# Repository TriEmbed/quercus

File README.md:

# Quercus (NOTE: Project name will change soon)
Quercus is a standalone system for developing for and using the combination of
a WIFI-capable ESP32 and one or more Renesas/Dialog mixed signal FPGA
chips. The FPGA synthesis tool has a drag and drop GUI that involves zero
Verilog or VHDL. It has a built in simulator and generates files that Quercus
can program in place in the user's system for simple FPGA applications. These
FPGAs are around one to two dollars in single quantity, even ones mounted on a
DIP board that can plug into a wireless breadboard. Quercus is aimed at making
FPGAs available to "the rest of us" while also creating a development ecosystem
to augment the Espressif IDF and Arduino IDE.

## User group
The user group kickoff meeting was held on 8/31/2022. Video here: https://youtu.be/zqejgwW3aIo

## Installation

### Linux

The first thing that should be done is run the script below with it's help
screen as such:

``` console
$ ./linux_install.sh --help
Usage: linux_install.sh -[3bcdhprstD] --[c3board,target-branch,config,device,help,wifi-passwd,rewrite-config,target,debug]
    -3 NUM | --c3board NUM              - The version of the que_purple board either 60 | 70, defaults to 70.
    -c FILE | --config FILE             - Optional config file, defaults to .quercusrc
    -d DEVICE | --device DEVICE         - Can be one of ESP32 | ESP32C3 | ESP32S2 defaults to ESP32C3.
    -h | --help                         - This screen.
    -p PASSWD | --wifi-passwd PASSWD    - The Password for the SSID.
    -r | --rewrite-config               - Reprompts for entries then rewrites the config file.
    -s SSID | --wifi-ssid SSID          - The WiFi SSID in the current network.
    -t TARGET_DIR | --target TARGET_DIR - The directory where the build will reside, defaults to /home/cnobile/.quercus.
    -D | --debug                        - Turn on DEBUG mode (propagates to the installit.sh script)..
    -n | --noop                         - The installit.sh script will not run, but the config may still be created.

    I2C pins as follows
    -------------------
      ESP32: SDA 18 SCL 19
    ESP32S2: SDA 1  SCL 0
    ESP32C3: SDA 18 SCL 19 (m80 60 rev)
             SDA 1  SCL 0  (m80 70 rev)
```

The ```linux_install.sh``` script can be run in multiple ways which will be
reviewed below. This script has the ability to create and use a config file.
The config file ```.quercusrc``` can be located in either the base of the
Quercus directory or in your user directory. The script will find the config
file in either place but will favor the Quercus directory.

1. To create a config file run the script with no arguments on the first
   run. If you need to rewrite the config file use the ```-r``` or 
   ```--rewrite-config``` argument.

   ``` bash
   $ ./linux_install.sh
   ```
   or
   ``` bash
   $ ./linux_install.sh -r
   ```
   The prompts will look similar to the ones below.
   ``` console
   Enter WiFi SSID or if exists Default () [Dd]: My-SSID
   Enter WiFi passwd or if exists Default () [Dd]: My-SSID-password
   Enter target device or Default (ESP32C3) [Dd]: ESP32
   Enter target directory or Default (/home/<user>/.quercus) [Dd]: /home/<user>/projects
   Enter target branch or Default (origin/release/v4.4) [Dd]: d
   ```
   Pressing **D** or **d** will use the default value. Use this if there is a
   default value between the **()**. Entering a space is NOT allowed and will
   cause the prompt to be displayed again. See 5 below.

   The generated config file will always be put in the base of the Quercus
   repository, if you want it in your user home directory you will need to
   manually move it there. The ```linux_install.sh``` script will find it as
   long as there is not a ```.quercusrc``` file in the Quercus directory.

2. You can also use a config file with a different name as shown below. This
   can allow you to have a config for many different physical environments. You
   must add the ```-r``` argument if you already have a ```.quercusrc``` file.

   ``` bash
   $ ./linux_install.sh -rc my_my.conf
   ```
   Just enter the filename **not** the full path as it will not be found. Once
   again it will be put into the base of the Quercus repository. It is
   advisable to move any of your own files to your user directory so it cannot
   be accidentally committed into the repository.

3. In all the cases above the script will run to completion after writing the
   config file. If you just want to write out the config file add a ```-n``` to
   the command line as below.

    ``` bash
    $ ./linux_install.sh -n
   ```
   This can be used with any other arguments. For example the ```-r``` argument
   so you can rewrite the config but not run the rest of the script.

4. You can also turn on debugging which can be used with any other arguments.

   ``` bash
   $ ./linux_install.sh -nD
   ```
   Assuming there is already a config file the above will just print out all
   the variable names and their values if any then exit. If you do not have a
   config file it will prompt for all values that are required and write them
   to the config file.

5. In some cases you may **not** want your WiFi credentials in a config file.
   To do this just type anything like the word **invalid** when prompted for
   either or both values then be sure to use the command line arguments ```-s
   <ssid>``` and ```-p <ssid password>``` to override what is in the config
   file.

   ``` bash
   $ ./linux_install.sh -r -s <my real SSID> -p <my real SSID password>
   ```
   ``` console
   Enter WiFi SSID or if exists Default () [Dd]: invalid
   Enter WiFi passwd or if exists Default () [Dd]: invalid
   ...
   ```
   The above command will force a rewrite of the config file then run the
   installation code. The ```-s <my real SSID>``` and ```-p <my real SSID
   password>``` arguments override the dummy SSID and it's password. This must
   be done every time you rerun the script if you have put dummy values in your
   config file.

All the remaining arguments are used to override what is in the config file and
will not be saved to the config file. As such you can use them to override any
or all arguments that are in the config file.

### Windows

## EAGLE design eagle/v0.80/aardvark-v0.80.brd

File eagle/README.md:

# Hardware CAD and related files for combination Espressif ESP32-C3-M1 (4M) and Dialog SLG47004V-DIP

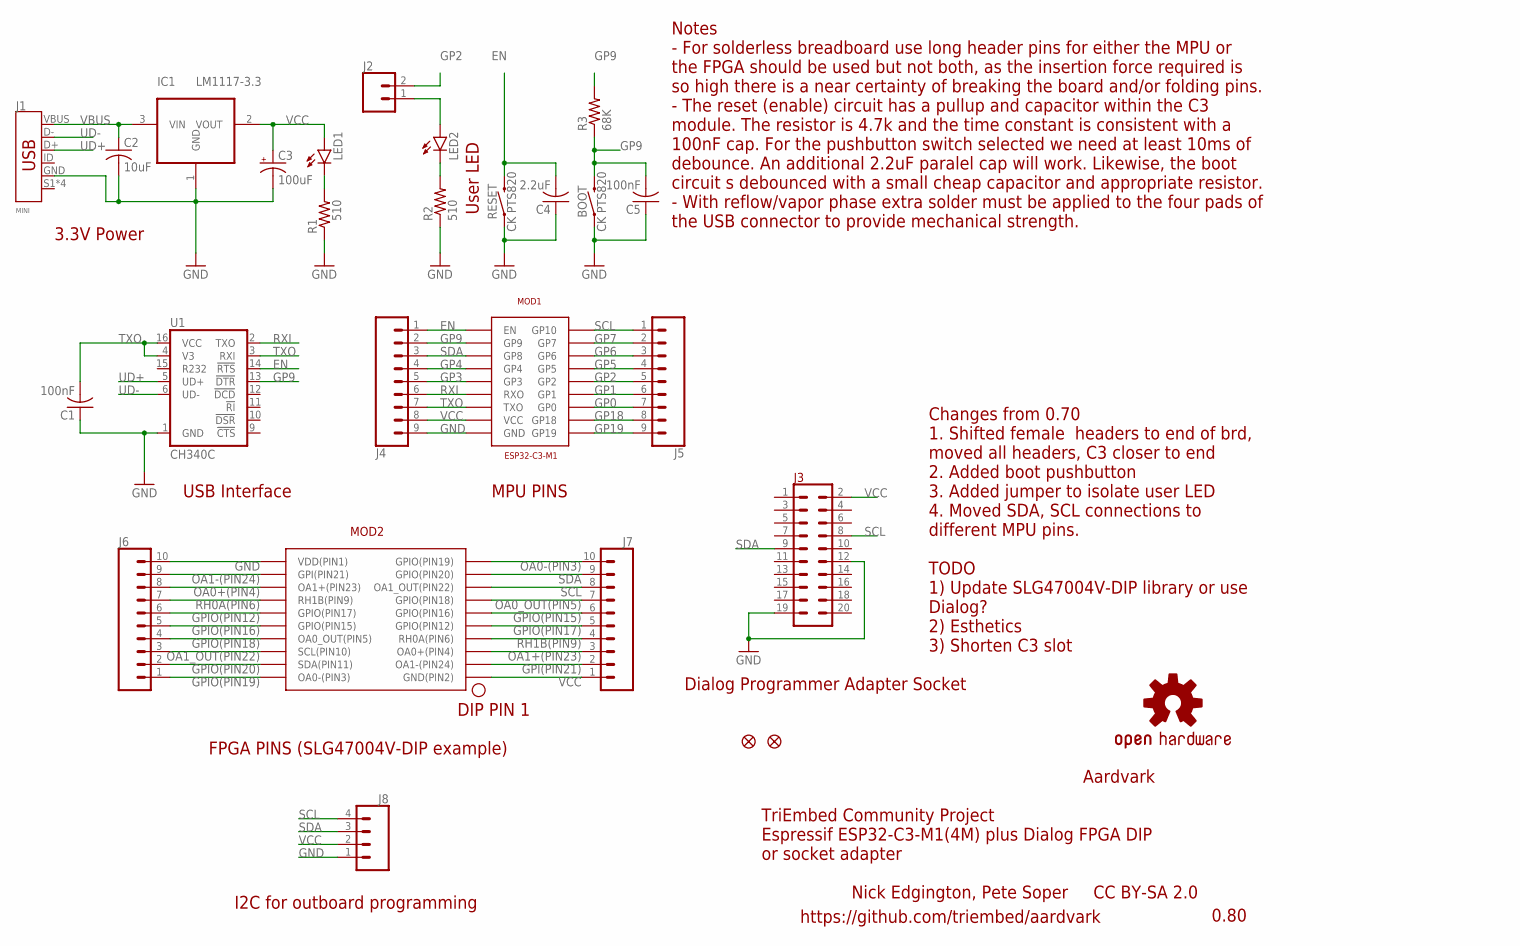
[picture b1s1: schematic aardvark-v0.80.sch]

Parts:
BOOT: CK PTS820; TACTILE_SWITCH_SMD_6.0X3.5MM
C1, C5: 100nF; C0805
C2: 10uF; C0805
C3: 100uF; PANASONIC_D
C4: 2.2uF; C0805
FD1, FD2: FIDUCIAL1X2; FIDUCIAL-1X2
IC1: LM1117-3.3; SOT223
J1: MINI; USB-MINIB
J2: CONN_02; 1X02
J3: CONN_10X2; 2X10
J4, J5: CONN_09NO_SILK; 1X09_NO_SILK
J6, J7: CONN_10NO_SILK_PTH_FEMALE; 1X10_NO_SILK
J8: CONN_041X04_NO_SILK; 1X04_NO_SILK
LED1, LED2: LEDCHIP-LED0805; CHIP-LED0805
LOGO1: OSHW-LOGOMINI; OSHW-LOGO-MINI
MOD1: ESP32-C3-M1; AITHINKER-C3-M1
MOD2: SLG47004V_DIP; SLG47004V-DIP
R1, R2: 510; R0805
R3: 68K; R0805
RESET: CK PTS820; TACTILE_SWITCH_SMD_6.0X3.5MM
U1: CH340C; SO016

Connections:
EN: C4.2, J4.1, MOD1.PIN1 (EN), RESET.2, U1.14 (!RTS)
GND: BOOT.1, C1.1, C2.2, C3.-, C4.1, C5.1, IC1.1 (GND), J1.GND, J3.12, J3.19, J4.9, J6.10, J8.1, MOD1.PIN9 (GND), MOD2.1 (VDD(PIN1)), R1.1, R2.1, RESET.1, U1.1 (GND)
GP0: J5.7, MOD1.PIN12 (GP0)
GP1: J5.6, MOD1.PIN13 (GP1)
GP2: J2.1, J2.2, J5.5, LED2.A, MOD1.PIN14 (GP2)
GP3: J4.5, MOD1.PIN5 (GP3)
GP4: J4.4, MOD1.PIN4 (GP4)
GP5: J5.4, MOD1.PIN15 (GP5)
GP6: J5.3, MOD1.PIN16 (GP6)
GP7: J5.2, MOD1.PIN17 (GP7)
GP9: BOOT.2, C5.2, J4.2, MOD1.PIN2 (GP9), R3.1, R3.2, U1.13 (!DTR)
GP18: J5.8, MOD1.PIN11 (GP18)
GP19: J5.9, MOD1.PIN10 (GP19)
GPI(PIN21): J7.2, MOD2.12 (OA1-(PIN24))
GPIO(PIN12): J6.6, MOD2.5 (GPIO(PIN17))
GPIO(PIN15): J7.6, MOD2.16 (GPIO(PIN16))
GPIO(PIN16): J6.5, MOD2.6 (GPIO(PIN15))
GPIO(PIN17): J7.5, MOD2.15 (GPIO(PIN12))
GPIO(PIN18): J6.4, MOD2.7 (OA0_OUT(PIN5))
GPIO(PIN19): J6.1, MOD2.10 (OA0-(PIN3))
GPIO(PIN20): J6.2, MOD2.9 (SDA(PIN11))
unnamed: LED2.C, R2.2
unnamed: LED1.C, R1.2
OA0+(PIN4): J6.8, MOD2.3 (OA1+(PIN23))
OA0-(PIN3): J7.10, MOD2.20 (GPIO(PIN19))
OA0_OUT(PIN5): J7.7, MOD2.17 (GPIO(PIN18))
OA1+(PIN23): J7.3, MOD2.13 (OA0+(PIN4))
OA1-(PIN24): J6.9, MOD2.2 (GPI(PIN21))
OA1_OUT(PIN22): J6.3, MOD2.8 (SCL(PIN10))
RH0A(PIN6): J6.7, MOD2.4 (RH1B(PIN9))
RH1B(PIN9): J7.4, MOD2.14 (RH0A(PIN6))
RXI: J4.6, MOD1.PIN6 (RXO), U1.2 (TXO)
SCL: J3.8, J5.1, J7.8, J8.4, MOD1.PIN18 (GP10), MOD2.18 (OA1_OUT(PIN22))
SDA: J3.9, J4.3, J7.9, J8.3, MOD1.PIN3 (GP8), MOD2.19 (GPIO(PIN20))
TXO: C1.2, J4.7, MOD1.PIN7 (TXO), U1.3 (RXI), U1.4 (V3), U1.16 (VCC)
UD+: J1.D+, U1.5 (UD+)
UD-: J1.D-, U1.6 (UD-)
VBUS: C2.1, IC1.3 (VIN), J1.VBUS
VCC: C3.+, IC1.2 (VOUT), J3.2, J4.8, J7.1, J8.2, LED1.A, MOD1.PIN8 (VCC), MOD2.11 (GND(PIN2))

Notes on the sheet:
0.80
Aardvark
TriEmbed Community Project Espressif ESP32-C3-M1(4M) plus Dialog FPGA DIP or socket adapter
Nick Edgington, Pete Soper CC BY-SA 2.0
https://github.com/triembed/aardvark
FPGA PINS (SLG47004V-DIP example)
MPU PINS
USB Interface
3.3V Power
User LED
Dialog Programmer Adapter Socket
I2C for outboard programming
Notes - For solderless breadboard use long header pins for either the MPU or the FPGA should be used but not both, as the insertion force required is so high there is a near certainty of breaking the board and/or folding pins. - The reset (enable) circuit has a pullup and capacitor within the C3 mo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
Changes from 0.70 1. Shifted female headers to end of brd, moved all headers, C3 closer to end 2. Added boot pushbutton 3. Added jumper to isolate user LED 4. Moved SDA, SCL connections to different MPU pins.
DIP PIN 1
TODO 1) Update SLG47004V-DIP library or use Dialog? 2) Esthetics 3) Shorten C3 slot

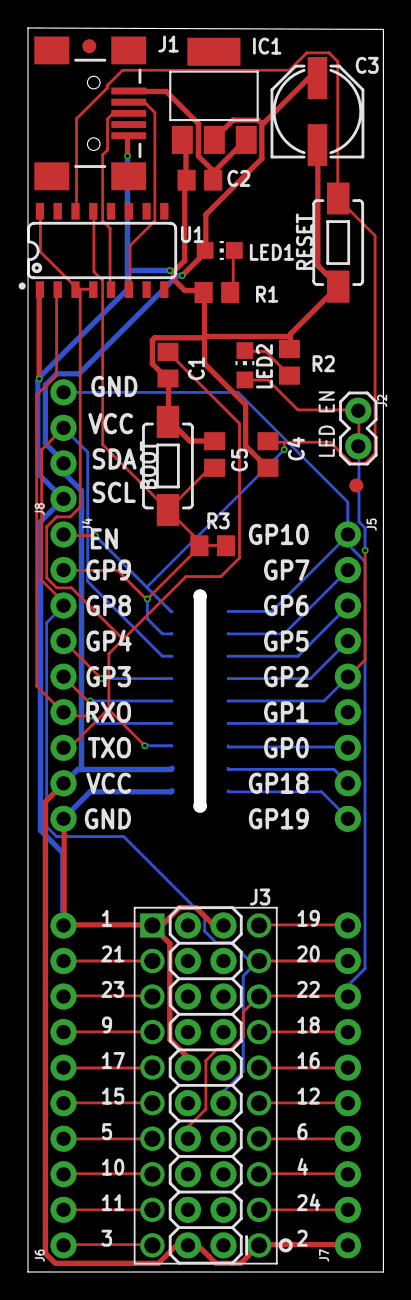
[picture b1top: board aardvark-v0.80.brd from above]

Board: 2 copper layers, 25.4 x 88.9 mm, 27 parts (1 on the bottom side), 39 nets.

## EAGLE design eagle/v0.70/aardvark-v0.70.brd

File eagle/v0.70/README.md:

# This is the 0.70 version of the ESP32 C3 + SLG47004V-DIP board.

## Changes since 0.60
1. Add switches for Enable, GPIO8, GPIO9 for reset and boot control
2. 4.7uF from Enable to ground to stretch it's time spent low
3. I2C pullups changed to 10k 'cause the signal paths are very short
4. Improve labeling
5. Spell aardvark correctly
6. Fix mirror image label ("GND")

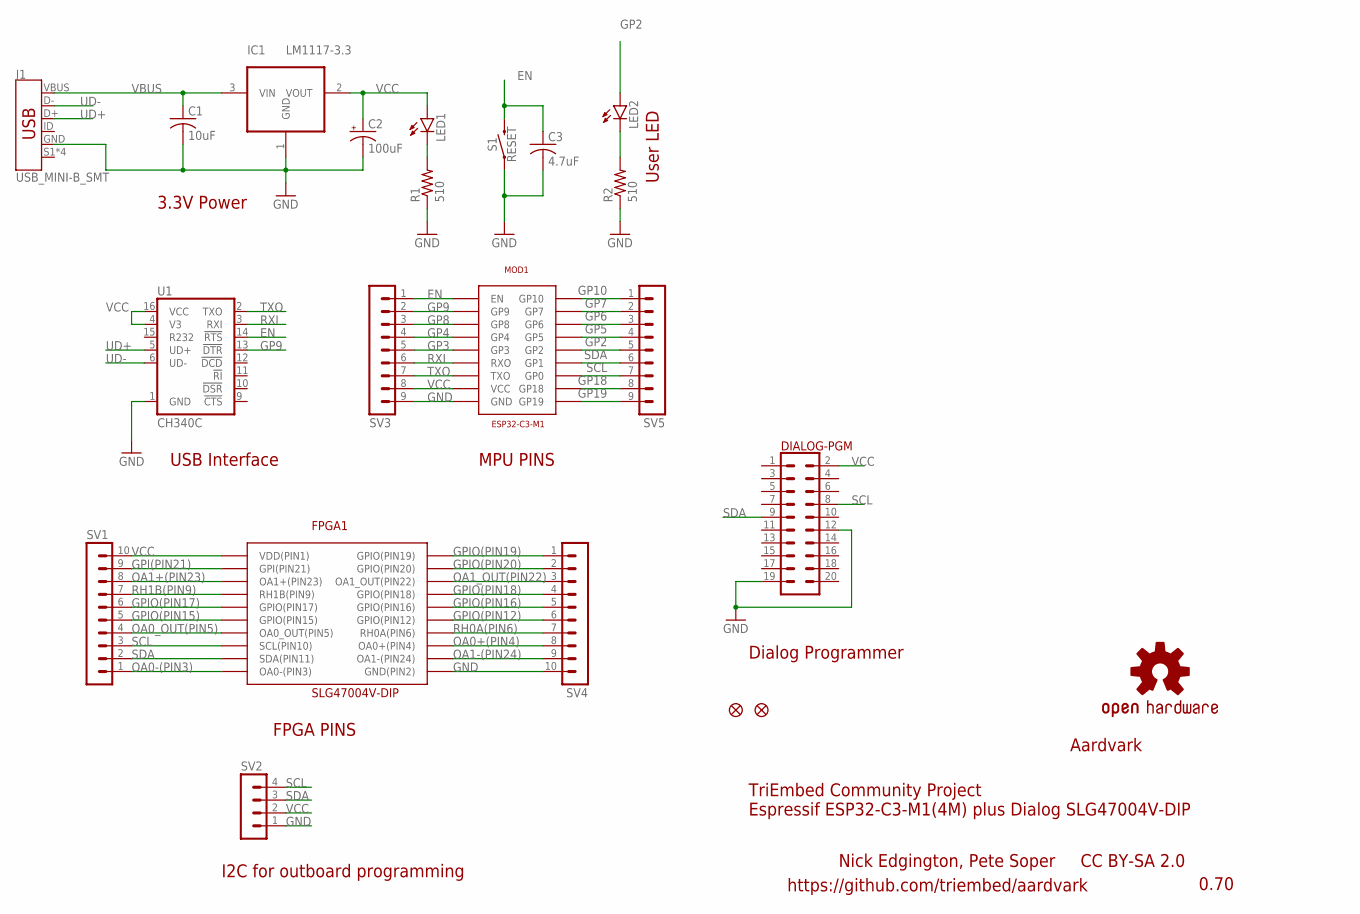
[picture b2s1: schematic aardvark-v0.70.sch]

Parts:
C1: 10uF; C0805
C2: 100uF; PANASONIC_D
C3: 4.7uF; C0805
DIALOG-PGM: CONN_10X2; 2X10
FD1, FD2: FIDUCIAL1X2; FIDUCIAL-1X2
FPGA1: SLG47004V-DIP
IC1: LM1117-3.3; SOT223
J1: USB_MINI-B_SMT; USB-MINIB
LED1, LED2: LEDCHIP-LED0805; CHIP-LED0805
LOGO1: OSHW-LOGOMINI; OSHW-LOGO-MINI
MOD1: ESP32-C3-M1; AITHINKER-C3-M1
R1, R2: 510; R0805
S1: RESET; TACTILE_SWITCH_SMD_6.0X3.5MM
SV1, SV4: MA10-1
SV2: MA04-1
SV3, SV5: MA09-1
U1: CH340C; SO016

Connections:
EN: C3.1, MOD1.PIN1 (EN), S1.2, SV3.1, U1.14 (!RTS)
GND: C1.2, C2.-, C3.2, DIALOG-PGM.12, DIALOG-PGM.19, FPGA1.11 (GND(PIN2)), IC1.1 (GND), J1.GND, MOD1.PIN9 (GND), R1.1, R2.1, S1.1, SV2.1, SV3.9, SV4.10, U1.1 (GND)
GP2: LED2.A, MOD1.PIN14 (GP2), SV5.5
GP3: MOD1.PIN5 (GP3), SV3.5
GP4: MOD1.PIN4 (GP4), SV3.4
GP5: MOD1.PIN15 (GP5), SV5.4
GP6: MOD1.PIN16 (GP6), SV5.3
GP7: MOD1.PIN17 (GP7), SV5.2
GP8: MOD1.PIN3 (GP8), SV3.3
GP9: MOD1.PIN2 (GP9), SV3.2, U1.13 (!DTR)
GP10: MOD1.PIN18 (GP10), SV5.1
GP18: MOD1.PIN11 (GP18), SV5.8
GP19: MOD1.PIN10 (GP19), SV5.9
GPI(PIN21): FPGA1.2 (GPI(PIN21)), SV1.9
GPIO(PIN12): FPGA1.15 (GPIO(PIN12)), SV4.6
GPIO(PIN15): FPGA1.6 (GPIO(PIN15)), SV1.5
GPIO(PIN16): FPGA1.16 (GPIO(PIN16)), SV4.5
GPIO(PIN17): FPGA1.5 (GPIO(PIN17)), SV1.6
GPIO(PIN18): FPGA1.17 (GPIO(PIN18)), SV4.4
GPIO(PIN19): FPGA1.20 (GPIO(PIN19)), SV4.1
GPIO(PIN20): FPGA1.19 (GPIO(PIN20)), SV4.2
unnamed: LED2.C, R2.2
unnamed: LED1.C, R1.2
OA0+(PIN4): FPGA1.13 (OA0+(PIN4)), SV4.8
OA0-(PIN3): FPGA1.10 (OA0-(PIN3)), SV1.1
OA0_OUT(PIN5): FPGA1.7 (OA0_OUT(PIN5)), SV1.4
OA1+(PIN23): FPGA1.3 (OA1+(PIN23)), SV1.8
OA1-(PIN24): FPGA1.12 (OA1-(PIN24)), SV4.9
OA1_OUT(PIN22): FPGA1.18 (OA1_OUT(PIN22)), SV4.3
RH0A(PIN6): FPGA1.14 (RH0A(PIN6)), SV4.7
RH1B(PIN9): FPGA1.4 (RH1B(PIN9)), SV1.7
RXI: MOD1.PIN6 (RXO), SV3.6, U1.3 (RXI)
SCL: DIALOG-PGM.8, FPGA1.8 (SCL(PIN10)), MOD1.PIN12 (GP0), SV1.3, SV2.4, SV5.7
SDA: DIALOG-PGM.9, FPGA1.9 (SDA(PIN11)), MOD1.PIN13 (GP1), SV1.2, SV2.3, SV5.6
TXO: MOD1.PIN7 (TXO), SV3.7, U1.2 (TXO)
UD+: J1.D+, U1.5 (UD+)
UD-: J1.D-, U1.6 (UD-)
VBUS: C1.1, IC1.3 (VIN), J1.VBUS
VCC: C2.+, DIALOG-PGM.2, FPGA1.1 (VDD(PIN1)), IC1.2 (VOUT), LED1.A, MOD1.PIN8 (VCC), SV1.10, SV2.2, SV3.8, U1.4 (V3), U1.16 (VCC)

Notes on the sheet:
0.70
Aardvark
TriEmbed Community Project Espressif ESP32-C3-M1(4M) plus Dialog SLG47004V-DIP
Nick Edgington, Pete Soper CC BY-SA 2.0
https://github.com/triembed/aardvark
FPGA PINS
MPU PINS
USB Interface
3.3V Power
User LED
Dialog Programmer
I2C for outboard programming

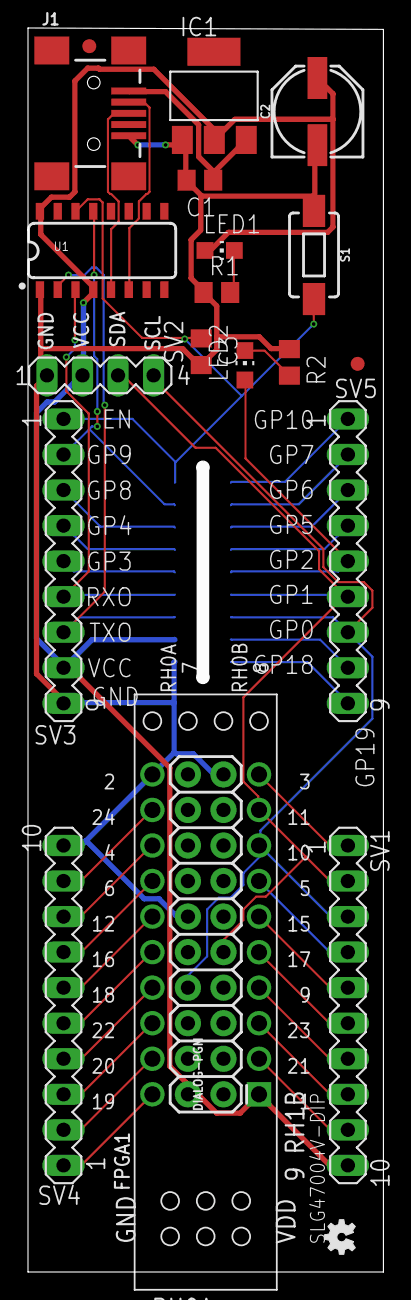
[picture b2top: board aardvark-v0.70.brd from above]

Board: 2 copper layers, 25.4 x 88.9 mm, 22 parts (0 on the bottom side), 39 nets.

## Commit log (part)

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2021-12-24 Clarification
2021-12-24 Defined versioning for README.md files
2021-12-24 test commit
2021-12-24 initial doc/contrib/Dialog/publications/README.md
2021-12-27 added doc/contrib/license/README.md
2021-12-30 prune junk
2021-12-30 additional MTP chips, prune junk
2021-12-30 doc/contrib/dialog/datasheets/README.md MTP part info
2021-12-31 added forum link to doc/contrib/dialog/publications/README.md
2021-12-31 Added oc/contrib/dialog/cad/GREENPAK.lbr, ditched useless part
2022-01-01 SLG46826G Breakout version 1.00
2022-01-01 dialog/SLG46826G-breakout version 1.00
2022-01-08 top level README.md update
2022-01-08 rename SLG46826G breakout directory
2022-01-08 rename breakout dir
2022-01-08 files moved from League repo
2022-01-08 C/C++ formatting script moved from League repo
2022-01-17 doc/contrib/ai-thinker/esp-c3-01m_specification.pdf
2022-01-19 doc/contrib/dialog/publications/SLG47004V_DIP_Proto_Board_Quick_Start_Guide.pdf
2022-01-19 removed obsolete programmer subdir
2022-01-26 Removed doc/contrib/gowin
2022-01-26 Culled irrelevant stuff from doc/contrib/dialog/datasheets
2022-01-26 updated doc/INVENTORY.md
2022-01-26 eagle/README.md wrestling
2022-01-26 culled doc/contrib/dialog/publications/README.md
2022-01-26 Added bug to README.md
2022-01-26 Added bugs and notes to top level README.md
2022-01-26 another attempt to comment out pictures
2022-01-26 images in eagle/README.md reenabled
2022-01-27 Added more bugs to top level README.md
2022-01-28 Added bugs and todo items to top level README.md. Could stand to be grouped together.
2022-01-28 added doc/README.md hyperlinks to ESP32 boot process details and little C3 dev board being used as a model implementation
2022-01-30 eagle/v0.70 initial
2022-01-31 fixed spelling error and mirror image GND designator
2022-01-31 more fixes doc'd in eagle/v0.70/README.md
2022-01-31 fixed, improved C3 Eagle lib
2022-01-31 rename C3 Eagle lib
2022-01-31 add OSH Park renderings of PCB top and bottom to eagle/v0.60
2022-01-31 boot/flash process steps put into doc/README.md
2022-02-01 Add note to bug pile item 0 in top level README.md
2022-02-01 added Eagle lib for the CH340C USB chip
2022-02-02 added Nanjin_Qinheng_Microelectronics CH340.pdf to doc/contrib
2022-02-02 added todo for adding a Dialog QFN socket/programmer footprint
2022-02-02 fixes to SLG47004V-DIP.lbr
2022-02-02 cleaned out obsolete notes
2022-02-02 Added more todos per Nick to README.md
2022-02-02 eagle/lib/README.md
2022-02-02 schematic update
2022-02-02 PDF of schematic
2022-02-02 new convension for PDFs foo-board.pdf instead of -layout.pdf
2022-02-02 really fix slot width
2022-02-02 added right angle header site for outboard I2C programming
2022-02-02 updated bug/todo list, added item for checking fit of programmer
2022-02-03 Noted shortening/narrowing of slot for C3
2022-02-03 confirmed Dialog programming socket board will not physically interfere
2022-02-04 doc/contrib/dialog/publications/README.md added URL for GreenPAKs by attribute
2022-02-04 aardvark v0.70 as shipped to OSH Park
2022-02-04 OSH Park renders of v0.70
2022-02-05 updated inventory
2022-02-06 eagle/v0.70/BOM.ods
2022-02-06 README.md updated
2022-02-06 initial firmware/README.md
2022-02-08 images/model-esp32-board.jpg has reset/boot circuit needed on our boards
2022-02-09 fixed PDFs
2022-02-09 added link to download page
2022-02-10 added three youtube videos to the bottom of doc/contrib/dialog/README.md
2022-02-11 ECOs added to eagle/v0.70/aardvark-v0.70-schematic.pdf
2022-02-11 example usage of v0.80 shown with aardvark-v0.80-board.pdf
2022-02-14 proper momentary and power switches for v0.80
2022-03-30 echidna concept2
2022-04-05 added Espressif datasheet local copy and URL
2022-04-08 eagle/v0.80 updated schematic todo list
2022-04-29 eagle/lib/{CK-ATS2D1G_NC_LFS.lbr,CK_JS202011SCQN.lbr} candidate switches
2022-05-15 English
2022-05-16 some tests need to looked into
2022-05-16 more tests issues
2022-05-19 working it
2022-05-24 doc/contrib/dialog/datashees/SLG47004V_DIP_Proto_Board_Quick_Start_Guide.pdf
2022-05-24 much cleaned up
2022-05-25 README.md with proto images
2022-05-25 cors data
2022-05-26 logo for repo
2022-05-26 tweak README.md
2022-05-28 doing stuff, menu source,
2022-05-29 dump working
2022-05-29 dump display
2022-05-30 name change to 'M80', corrections, pruned mboard
2022-05-31 first
2022-05-31 good
2022-06-01 Changed to use idf install environemnt variable "the-ant" build no longer requires cmake file rewrite for different installation locations of esp-idf
2022-06-02 temp file foo
2022-06-02 Update README.md
    Zapped obsolete photos
2022-06-16 initial, incomplete
2022-06-16 v0.02 handle prerequist packages, v5.0->python 3.10, env var to control output verbosity
2022-06-22 linux/installit 0.03 partially tested
2022-06-23 linux/installit 0.05 tested well enough to start using: nvm/npm still to come
2022-06-24 linux/{installit,cleanit} functionally complete, ready for full testing
2022-06-24 linux/installit add -y to apt install (Nick)
2022-06-24 linux/installit msg about how long submodules take (Nick)
2022-06-25 update LICENSE (needs discussion)
2022-06-25 simplify option handling, add design related remarks toward the top
2022-06-25 update notes, switch handler, finish more work on cleanit: untested
2022-06-26 linux/installit add npm run builds, fix direnv, add idf.py build in the-ant
2022-06-26 linux/installit removed -x bash option, fixed a bunch of bugs.
2022-06-27 main/i2c.h externs
2022-06-28 Fix web deploy to use SPI nor
2022-06-29 linux/installit 0.16 filled in a lot of needed functionality to edit the-ant config files according to chip type and other factors, require local router SSID and password, C3 M80 version x 100 (i.e. 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
2022-06-29 main/Kconfig.projbuild add TARGETSDA, TARGESCL for real this time
2022-06-29 linux/installit more bug fixes. Seems to work
2022-06-30 Fixes for small syntax breakages that got into the file over time
2022-06-30 some optimizations
2022-06-30 in src/api/project.js replace 192.168.4.1 w BASEIP
2022-06-30 updated README.md with homebrew dev board instructions and instructions for connecting a Dialog SLG47004V-DIP for the blinky application
2022-07-01 README.md updated with more how-to
2022-07-04 Add autoconfiguration import, (commented out) support for mdns
2022-07-04 sdkconfig sync with current menuconfig state
2022-07-04 sdkconfig.old preserve
2022-07-04 linux/installit 0.24 mdns support (not yet working), always clone aardvark and the-ant 'cause too hard to track their mutations by the script, don't depend on matching Nick router labels, tidy up
2022-07-04 append slash to urls
2022-07-04 main/i2c.c remove blasted pin assignments again
2022-07-04 handle leading -version or -help in command line
2022-07-05 Fix import and use of autoconfiguration object
2022-07-05 fix specific MAC addr fetched in mdns initialization
2022-07-06 Update installit
    add
2022-07-06 add missing closing quote to echo
2022-07-07 switch to que_ prefixes for project component names
2022-07-07 removed obsolete hardware/aardvark/README.md
2022-07-07 scripts/README.md brought up to date
2022-07-07 add main/mdns.h
2022-07-07 main/ant_main.c comment out mdns refs while Espressif esp-idf repo is broken
2022-07-07 linux/installit 0.28 fix .envrc
2022-07-08 renames and refinements
2022-07-08 renaming/refining
2022-07-09 add aardvark-screen/image0.png to show initial screen shown (most?) of the time
2022-07-09 update aardvark-screens with missing initial aardvark web screen that might appear before next one
2022-07-09 update README.md w new user manual URL
2022-07-09 renaming
2022-07-09 Change license to CC0
2022-07-12 Put default router SSID and password match pattern back
2022-07-12 linux/installit 0.29 source .bashrc in case direnv installed
2022-07-13 linux/installit 0.30 fix bug where .bashrc sourced after direnv completion put into it
2022-07-14 lets not make the map files.
2022-07-19 Complete attribution
2022-07-26 Add QuercusUserManual.{odt,html} to top level
2022-07-26 fix missing image
2022-07-29 issue #6 linux/installit correct git branch setting
2022-08-02 push files down to aardvark
2022-08-02 push files down to ant
2022-08-02 push files down to breakouts
2022-08-02 push files down to purple
2022-08-02 push files down to tools
2022-08-03 LICENSE: add CC0 for hardware, updates
2022-08-03 purge obsolete LICENSE files
2022-08-04 Update README.md
    A few pitiful changes in a sea of needs.
2022-08-12 issue7
2022-08-14 issue #25 how to for pull requests version 0.01 assigned to Ron Craig and Pete Soper
2022-08-15 Initial version of test script to ultimately become installit.ps1
2022-08-15 issue25 push pullrequestprocess dir down under doc
2022-08-19 doc/pullrequests/README.md is incomplete draft
2022-08-20 issue #29 fixed pinout, added board pic
2022-08-22 docs:add CONTRIBUTING.md
    Add instructions on how to contribute fixes and features to the project.
    Fixes #25
2022-08-23 Create REPORT-BUG.yml
    Initial partial drop
2022-08-23 Create config.yml
    Add links directing folk to useful resources
    Addressing Issue #32
2022-08-23 Create support-question.md
    Starter template for support questions
2022-08-23 issue25: update pull request directions
2022-08-23 Delete pull_request_template.yml
    Github doesn't support yml for PR templates. <sigh>
    Issue35
2022-08-23 issue35: add Contrib Lic Agreement to doc/
2022-08-24 add additional photo
2022-08-24 fix markdown
2022-08-24 update image size
2022-08-24 scale image
2022-08-27 Issue 38: Update feature-request.yml
    Tiny change- clarify PR field's purpose
2022-08-27 Update and rename support-question.md to support-question.yml
    Issue 33: convert to yml to remove Edit / Preview tabs.
2022-08-27 Update and rename REPORT-BUG.yml to report_bug.yml
    Issue #32 incorporate Pete's suggestions
2022-08-27 #38: Update and rename feature_request.yml
    Tweaks per input from Pete.
2022-08-27 Update README.md
    Testing PR.
2022-08-27 Update and rename support-question.yml to support_question.yml
    Issue #33
    rename to match standards
    Make it clear existing resource links are place holders
2022-08-27 Update config.yml
    #37 add link to doc/faq.md per Pete's suggestion
2022-08-27 Update config.yml
    #37 add link to FAQ per Pete's suggestion.
2022-08-27 #40 Create faq.md
    Created template file.
    Closes #40
2022-08-27 #35 Delete cla from doc folder
    CLA is stored externally at https://gist.github.com/FrugalGuy/2ffa493e842ce030d9384caea7d00971
    CLA spelling errors corrected.
2022-08-29 Fixed a few issues in the installit.sh script and added the remaining two arguments to the call to installit.sh.
2022-08-29 Added a LF so it looks the same as the original.
2022-08-29 Checkpoint for test.ps1 Add cleanup.ps1 script Add win_install.bat
2022-08-30 Updated the help screen menu of items.
2022-08-31 doc/presentations/20220831-InstallSteps.{odp,pdf}
2022-09-02 Latest updates.
2022-09-04 Looks like it's working with a fresh build, but still needs additional testing.
2022-09-04 Opps, forgot to fix the variables used in the help text.
2022-09-04 Fixed some missing quotes.
2022-09-05 Moved the sanity checks out of the CLI interpreter and run it later in the process.
2022-09-06 Fixed the spelling of Linux, duh.
2022-09-10 #43 new hardware/README.md
2022-09-11 #44 README.md name change notice and user group section
2022-09-12 #45 next purple will have a DBUS connector
2022-09-12 #47 mention 1.00 in hardware/purple/README.md
2022-09-12 #47 hardware/purple/eagle/v1.00/\*
2022-09-12 #47 hardware/README.md more requirements
2022-09-14 #48 rename/fix/enhance purple 1.00 enumeration in hardware/README.md
2022-09-15 All files with the word 'lock' in its name will be ignored.
2022-10-06 #50 hardware/purple/README.md update 1.00 Purple
2022-10-06 #50 Serial JTAG & requested TODO item
2022-10-06 #50 move purple reqs back to hardware/purple/README.md
2022-10-07 Update to the README.md.
2022-10-07 Updated to both the README.md and linux_install.sh.
2022-10-08 Fixed how the help screen exits.
2022-10-08 Removed some whitespace.
2022-10-08 Fixed a few issues with how the config file worked and updated the README.md file.

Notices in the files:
parts and their libraries:
SparkFun-Switches: Licensing: Creative Commons ShareAlike 4.0 International - https://creativecommons.org/licenses/by-sa/4.0
apexprotofactory: Author, license:
